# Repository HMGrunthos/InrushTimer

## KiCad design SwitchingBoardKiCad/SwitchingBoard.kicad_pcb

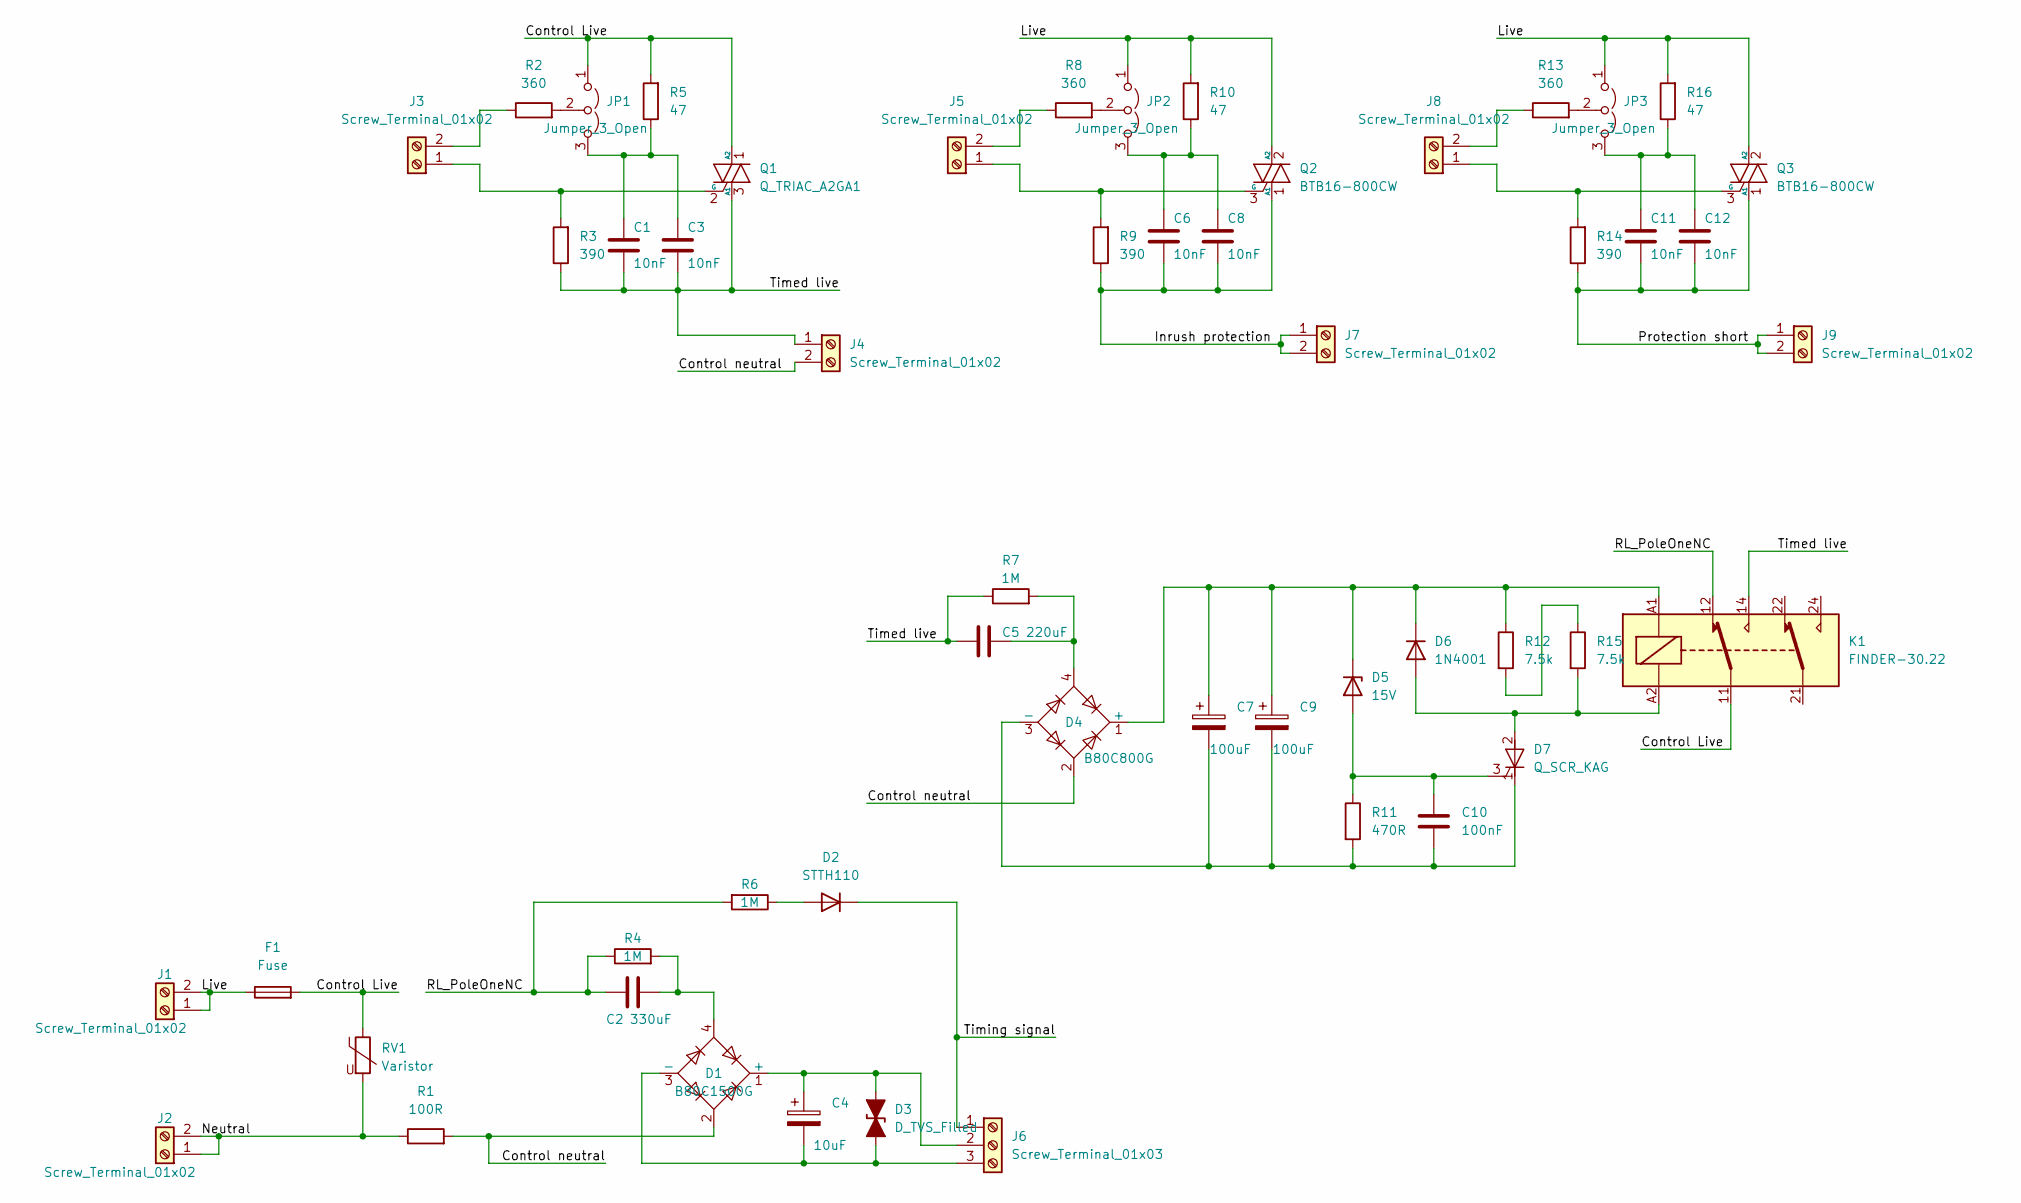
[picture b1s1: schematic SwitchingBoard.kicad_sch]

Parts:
C1, C3, C6, C8, C11, C12: 10nF; C_Rect_L18.0mm_W5.0mm_P15.00mm_FKS3_FKP3
C2: 330uF; C_Rect_L18.0mm_W9.0mm_P15.00mm_FKS3_FKP3
C4: 10uF; CP_Radial_D5.0mm_P2.00mm
C5: 220uF; C_Rect_L26.5mm_W6.0mm_P22.50mm_MKS4
C7, C9: 100uF; CP_Radial_D6.3mm_P2.50mm
C10: 100nF; C_Disc_D5.0mm_W2.5mm_P5.00mm
D1: B80C1500G; Diode_Bridge_Round_D9.8mm
D2: STTH110; D_DO-41_SOD81_P10.16mm_Horizontal
D3: D_TVS_Filled; D_DO-15_P12.70mm_Horizontal
D4: B80C800G; Diode_Bridge_Round_D9.8mm
D5: 15V; D_DO-35_SOD27_P7.62mm_Horizontal
D6: 1N4001; D_DO-41_SOD81_P10.16mm_Horizontal
D7: Q_SCR_KAG; TO-220-3_Horizontal_TabDown
F1: Fuse; Fuseholder_Clip-5x20mmOr6.3x32_Schurter_OG_Lateral_P20.00x5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
J1, J2, J3, J4, J5, J7, J8, J9: Screw_Terminal_01x02; TerminalBlock_Altech_AK300-2_P5.00mm
J6: Screw_Terminal_01x03; TerminalBlock_Altech_AK300-3_P5.00mm
JP1, JP2, JP3: Jumper_3_Open; TerminalBlock_4Ucon_1x03_P3.50mm_Horizontal
K1: FINDER-30.22; Relay_DPDT_Finder_40.52
Q1: Q_TRIAC_A2GA1; TO-92L_Inline
Q2, Q3: BTB16-800CW; TO-220-3_Vertical
R1: 100R; R_Axial_Power_L20.0mm_W6.4mm_P22.40mm
R2, R8, R13: 360; R_Axial_DIN0207_L6.3mm_D2.5mm_P10.16mm_Horizontal
R3, R9, R14: 390; R_Axial_DIN0207_L6.3mm_D2.5mm_P10.16mm_Horizontal
R4, R6, R7: 1M; R_Axial_Power_L20.0mm_W6.4mm_P22.40mm
R5, R10, R16: 47; R_Axial_DIN0207_L6.3mm_D2.5mm_P10.16mm_Horizontal
R11: 470R; R_Axial_DIN0207_L6.3mm_D2.5mm_P10.16mm_Horizontal
R12, R15: 7.5k; R_Axial_DIN0207_L6.3mm_D2.5mm_P10.16mm_Horizontal
RV1: Varistor; RV_Disc_D12mm_W4.3mm_P7.5mm

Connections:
/Control Live: F1.2, JP1.1 (A), K1.11, Q1.1 (A2), R5.2, RV1.1
/Control neutral: D1.2, D4.2, J4.2, R1.2
/Inrush protection: C6.1, C8.1, J7.1, J7.2, Q2.1 (A1), R9.1
/Live: F1.1, J1.1, J1.2, JP2.1 (A), JP3.1 (A), Q2.2 (A2), Q3.2 (A2), R10.2, R16.2
/Neutral: J2.1, J2.2, R1.1, RV1.2
/Protection short: C11.1, C12.1, J9.1, J9.2, Q3.1 (A1), R14.1
/RL_PoleOneNC: C2.1, K1.12, R4.1, R6.2
/Timed live: C1.1, C3.1, C5.1, J4.1, K1.14, Q1.3 (A1), R3.1, R7.1
/Timing signal: D2.1 (K), J6.1
unnamed: C1.2, C3.2, JP1.3 (B), R5.1
unnamed: C2.2, D1.4, R4.2
unnamed: C4.1, D1.1 (+), D3.2 (A2), J6.2
unnamed: C4.2, D1.3 (-), D3.1 (A1), J6.3
unnamed: C5.2, D4.4, R7.2
unnamed: C6.2, C8.2, JP2.3 (B), R10.1
unnamed: C7.1, C9.1, D4.1 (+), D5.1 (K), D6.1 (K), K1.A1, R12.1
unnamed: C7.2, C9.2, C10.1, D4.3 (-), D7.1 (K), R11.2
unnamed: C10.2, D5.2 (A), D7.3 (G), R11.1
unnamed: C11.2, C12.2, JP3.3 (B), R16.1
unnamed: D2.2 (A), R6.1
unnamed: D6.2 (A), D7.2 (A), K1.A2, R15.2
unnamed: J3.1, Q1.2 (G), R3.2
unnamed: J3.2, R2.1
unnamed: J5.1, Q2.3 (G), R9.2
unnamed: J5.2, R8.1
unnamed: J8.1, Q3.3 (G), R14.2
unnamed: J8.2, R13.1
unnamed: JP1.2 (C), R2.2
unnamed: JP2.2 (C), R8.2
unnamed: JP3.2 (C), R13.2
unnamed: R12.2, R15.1

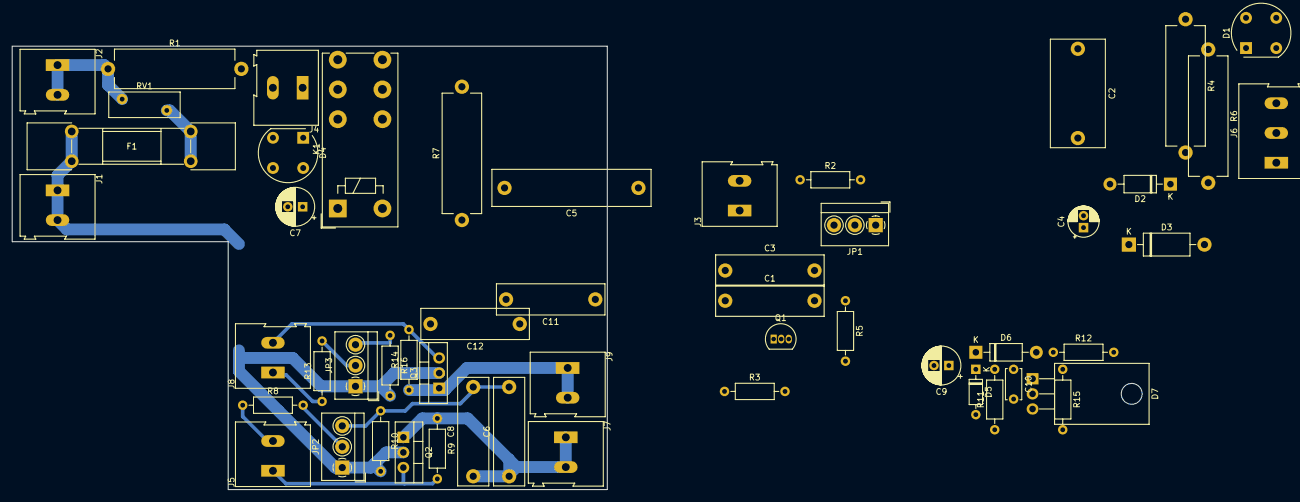
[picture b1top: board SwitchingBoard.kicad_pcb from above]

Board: 2 copper layers, 100.0 x 74.5 mm, 53 parts (0 on the bottom side), 31 nets.

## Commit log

2018-07-06 Adding all inrush timer design files and libraries
2018-07-11 Added peak detector opamps
2018-07-13 Still playing with 555 design, peak detector clock seems OK
2018-07-19 Finalised the peak detector, reworked the 555 trigger section.
2018-07-23 Timing flipflops nearly completed
2018-08-28 Updating prior to PCB layout
2018-08-28 Added 3.6V zenner
2022-04-25 Tweaked design and updated component footprints
2022-04-28 Adding relay delay module and updates to inrush timer.
2022-04-28 Updating with inrush model and chenges to cap values to support additional triac channel
2022-04-30 Committing first cut of the board design. Two control signals unrouted.
2022-05-01 Updated some component values and squished the timers further to the right.
2022-05-01 Initial version of routed PCB. All traces routed and passes cursory DRC.
2022-05-01 Tweaked layout to meet more exacting design rules.
2022-05-01 Fixed missing track. Tweaked track widths.
2022-05-01 Adding artwork file.
2022-05-01 Adding script to combine PDFs from quadrants (to save on transparencies)
2022-05-01 Fixed an incorred footprint.
2022-05-01 Updated artwork.
2022-05-02 Tidied up some traces and improved trace seraration.
2022-05-03 Trace adjustments.
2022-05-03 Added artwork for the stop mask
2022-05-04 Adding switching board design.
2022-05-04 Updated schematics and parts for the switching board.
2022-05-05 Checking in first version of the switching board layed out in KiCad
2022-05-05 KiCad switching board schematic passes initial ERC.
2022-05-05 Assigned footprints
2022-05-05 Initial grouping of components on PCB
2022-05-07 Tweaked layout based on autorouter run.
2022-05-07 Updated artwork
2022-05-07 Updated schematics and board to address error in aux output assignment.
2022-05-12 Committing changes to circuit to remove a time and put the optoisolators into series.
2022-05-12 Fixed reset generator.
2022-05-12 Simplified resistive divider setup.
2022-05-13 Updated model and board with circuit and component values.
2022-05-13 Changed gate resistors and checked component values.
2022-05-13 Added inductor model and tweaked schematic.
2022-05-14 Fixed inverted comparator and actually calculated hysteresis resistors!
2022-05-14 Updated values and topology on schematic.
2022-05-14 Corrected component values (units)
2022-05-14 Tidied up model schematic.
2022-05-14 Updated optotriac symbol
2022-05-14 Fixed missing libraries by moving parts into local lib. Renumbered components.
2022-05-14 Updated component packages
2022-05-14 Updated zener model and added annotation on schematic.
2022-05-15 Added measurements for peak clock rise and fall time. Tidied up library imports. Sorted out gate capacitance on output of comparator.
2022-05-15 Tweaked convergence option and changed zenner follower to ZTX451
2022-05-15 Removed ||'ll resistance for looking at peak voltage. Removed unused models.
2022-05-15 Re-layed out peak detector, supply and reset generator.
2022-05-15 Layout changes.
2022-05-16 Removed optocoupler from this board and updated the fuseholder footprint.
2022-05-17 ayed out the timer - starting on the D types. Fixed incorrect gate capacitance.
2022-05-17 Added custom fuse footprint and updated PCB.
2022-05-17 Refitted the timer and pulse generator.
2022-05-17 Everything on the board - not routed.
2022-05-17 Added a couple more power routes.
2022-05-18 First complete routing fit. Passes design rules.
2022-05-18 Slight track style tweaks.
2022-05-20 Pushed some tracks to the bottom side
2022-05-20 Adjusted resistor value
2022-05-20 Shifted component to the bottom layer and adjusted some track placements.
2022-05-20 Track and component positions.
2022-05-20 Tidied up component and track placement.
2022-05-20 Rev two layout - minor change to track angle
2022-05-20 Rev two masks
2022-05-23 Added photo of PCB processing notes.
2022-05-25 Changed pass element to TIP41C and moved some components around to make more space.
2022-05-25 Rerouted power supply section and made some space around the pot.
2022-05-25 Fixed some component orientations.
2022-05-26 Tweaked ground and component positions - still to do; adjust pad sizes.
2022-05-27 Increased TH pad sizes and adjusted component positions to pass DRC.
2022-05-27 Adding updated artwork.
2022-05-29 Tweaked track position.
2022-06-01 Playing with layout and routing in KiCad
2022-06-03 Shuffled component placement to avoid via.
2022-06-03 Fixed TRIAC symbol and tweaked layout further.
2022-08-25 Added duplicated resistors to hit worst case voltage ratings.
2022-10-17 Fixed up silkscreen and added job file from JLCPCB
2022-10-17 More silkscreen fixes.
2022-10-18 Checked in gerber files for inrush timer production.
2022-12-14 Fixed schematic connections.
2024-02-17 Added missing diode model
2024-02-17 Attempt to fix a reported issue with the diode syntax in pspice.
